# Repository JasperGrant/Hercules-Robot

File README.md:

# Hercules Robot

Seen here with sunglasses

Design project for ECED3901.

2nd place winner of the Gregson Robotic Design Competition.

Team consists of Andy Doucet, Spencer Dugas, and Jasper Grant.

# Problem

The goal of the project is to create a robot to autonomously capture and dispose of mines while navigating a maze and avoiding wildlife.

The robot will have to deal with randomly placed mines that must be defused before contact is made, and wildlife in the form of a carboard deer cutout which walks back and forth through the maze using a pulley system.

# High Level Robot Architecture

# Solution

Our robot's control code consisted of an esoteric programming language in which a 3x7x7 array of characters is interpreted as an executable. This array can be filled with cardinal directions or other symbols. Each array element points to the next element to be executed.

Once a mine is detected by the robot's limit switches, the robot will switch from following the forwards array, to the return array until the mine has been disposed of. Finally the robot will follow a third return array back to it's next position in the mine hunt.

The final program used for competition:
char map[NUMBEROFMAPS][MAPSIZE][MAPSIZE][MAXSTRINGLEN] = {
	"N", "E", "E", "S", "S", "N", "E",
  "", "E", "N", "M", "W", "W", "SEE",
  "", "N", "N", "N", "W", "W", "S",
  "", "", "", "", "", "M", "W",
  "", "", "", "N", "N", "E", "W",
  "", "", "", "M", "S", "N", "W",
  "", "", "N", "N", "W", "", "",
  
  "", "E", "N", "N", "E", "E", "S",
  "", "E", "W", "N", "E", "E", "S",
  "", "N", "e", "S", "S", "N", "E",
  "", "", "", "", "", "E", "E",
  "", "", "E", "S", "S", "S", "S",
  "", "", "R", "S", "E", "S", "S",
  "", "", "W", "S", "S", "", "",
  
  "", "WwNF", "WwNNWWSSEF", "WwNNWWSSF", "WwNNWWSF", "NNNWWH", "NNNWWH",
  "", "WwNF", "WwNNWSF", "EF", "WwNNWWF", "NNNWWH", "NNNWWH",
  "", "WwNF", "WwNF", "WwNNF", "WwNNWF", "NNNNWWWSWF", "NNNNWWWSF",
  "", "", "", "", "", "ENNF", "NNNNWWWF",
 	"", "", "", "WNNF", "WNNNF", "NNNF", "NNNNWWF",
  "", "", "", "WNF", "NF", "NNNNF", "NNNNWF",
  "", "", "ENF", "ENNF", "ENNWF", "NNNWWWWF", "NNNWWWWF"};
 
 # Optimization
 
 Path planning was done using Adaptive Monte Carlo Localization on a constantly kept up to date LIDAR map.
 Included in the repo also the most up to date and successful pathfinding parameters.

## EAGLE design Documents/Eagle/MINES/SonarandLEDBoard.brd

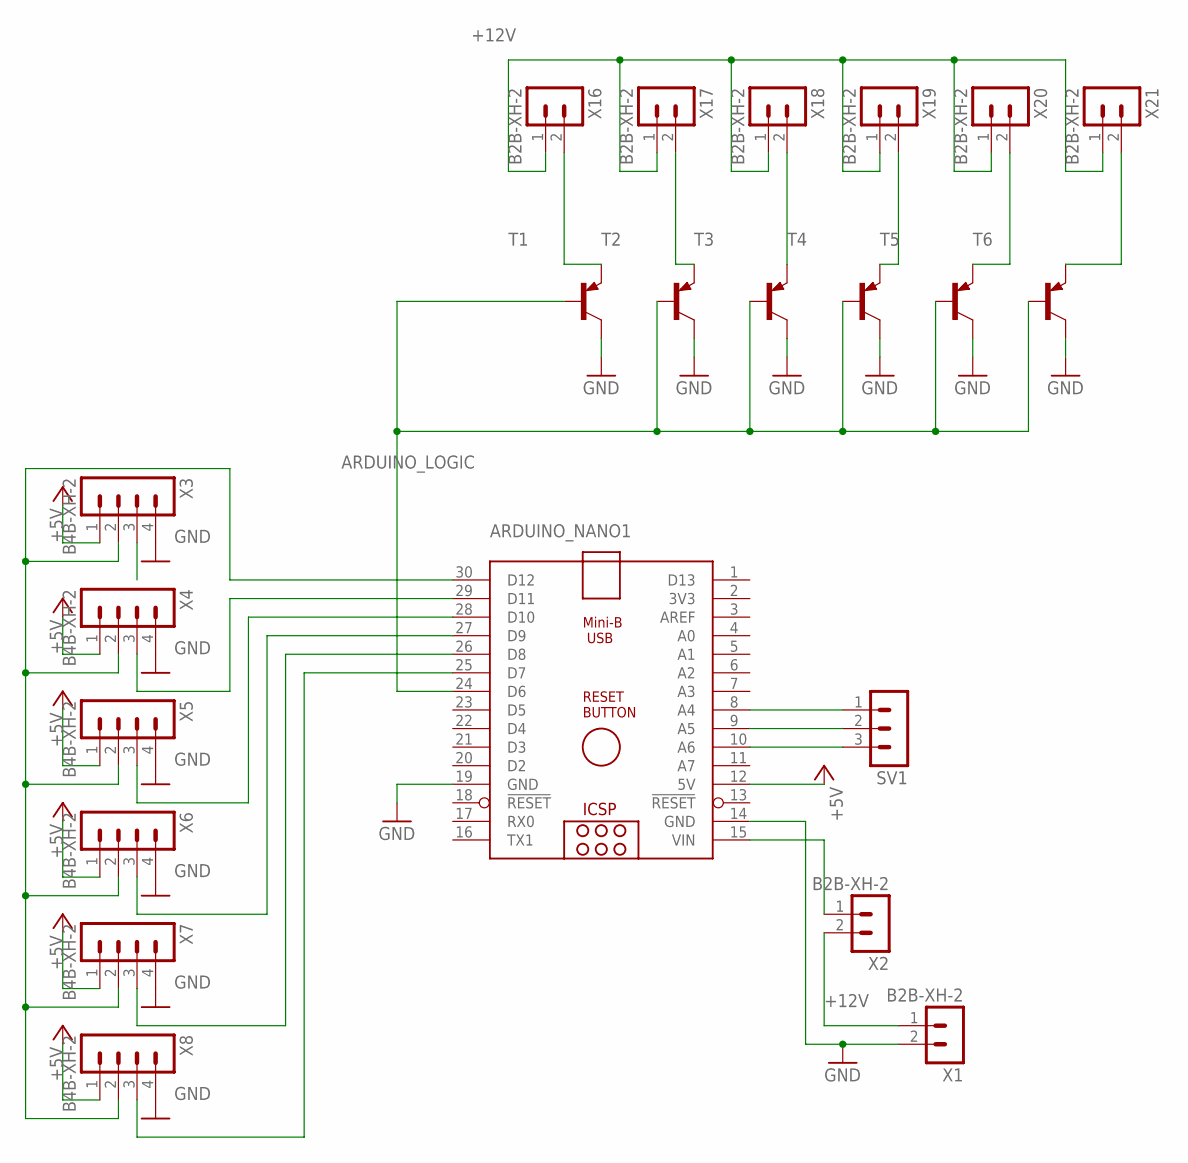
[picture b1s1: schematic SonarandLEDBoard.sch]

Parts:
ARDUINO_NANO1: ARDUINO_NANO
SV1: MA03-1
T1, T2, T3, T4, T5, T6: -PNP-TOP3V; TOP3V
X1, X2, X16, X17, X18, X19, X20, X21: B2B-XH-2; B2B-XH-A
X3, X4, X5, X6, X7, X8: B4B-XH-2; B4B-XH-A

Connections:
+5V: ARDUINO_NANO1.12 (5V), X3.1, X4.1, X5.1, X6.1, X7.1, X8.1
+12V: X1.1, X2.2, X16.1, X17.1, X18.1, X19.1, X20.1, X21.1
ARDUINO_LOGIC: ARDUINO_NANO1.24 (D6), T1.B, T2.B, T3.B, T4.B, T5.B, T6.B
GND: ARDUINO_NANO1.14 (GND), ARDUINO_NANO1.19 (GND), T1.C, T2.C, T3.C, T4.C, T5.C, T6.C, X1.2, X3.4, X4.4, X5.4, X6.4, X7.4, X8.4
unnamed: ARDUINO_NANO1.8 (A4), SV1.1
unnamed: ARDUINO_NANO1.15 (VIN), X2.1
unnamed: ARDUINO_NANO1.9 (A5), SV1.2
unnamed: ARDUINO_NANO1.10 (A6), SV1.3
unnamed: T1.E, X16.2
unnamed: ARDUINO_NANO1.26 (D8), X7.3
unnamed: ARDUINO_NANO1.29 (D11), X4.3
unnamed: ARDUINO_NANO1.28 (D10), X5.3
unnamed: T2.E, X17.2
unnamed: ARDUINO_NANO1.27 (D9), X6.3
unnamed: T3.E, X18.2
unnamed: T4.E, X19.2
unnamed: ARDUINO_NANO1.30 (D12), X3.2, X4.2, X5.2, X6.2, X7.2, X8.2
unnamed: ARDUINO_NANO1.25 (D7), X8.3
unnamed: T5.E, X20.2
unnamed: T6.E, X21.2

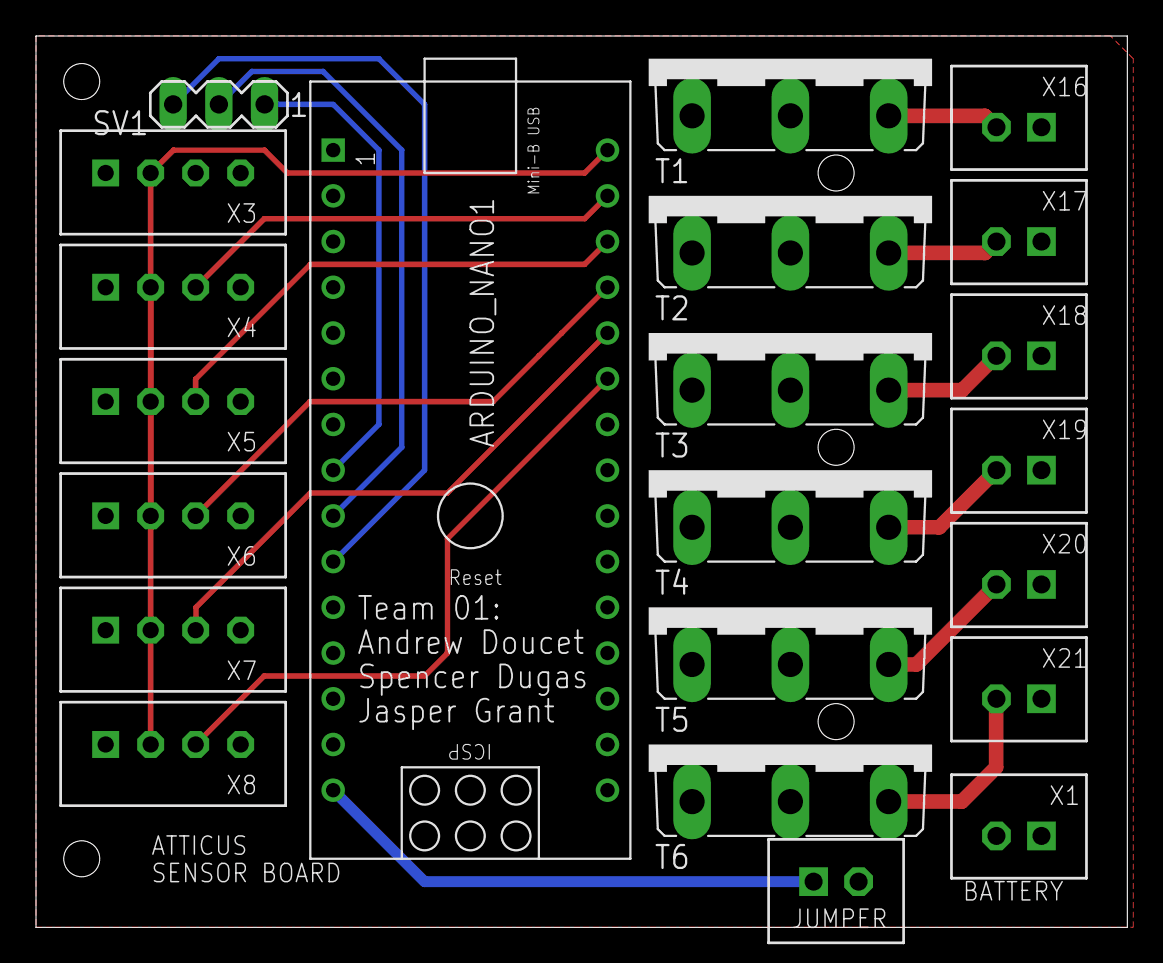
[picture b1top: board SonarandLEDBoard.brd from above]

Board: 2 copper layers, 60.6 x 49.5 mm, 22 parts (0 on the bottom side), 20 nets.

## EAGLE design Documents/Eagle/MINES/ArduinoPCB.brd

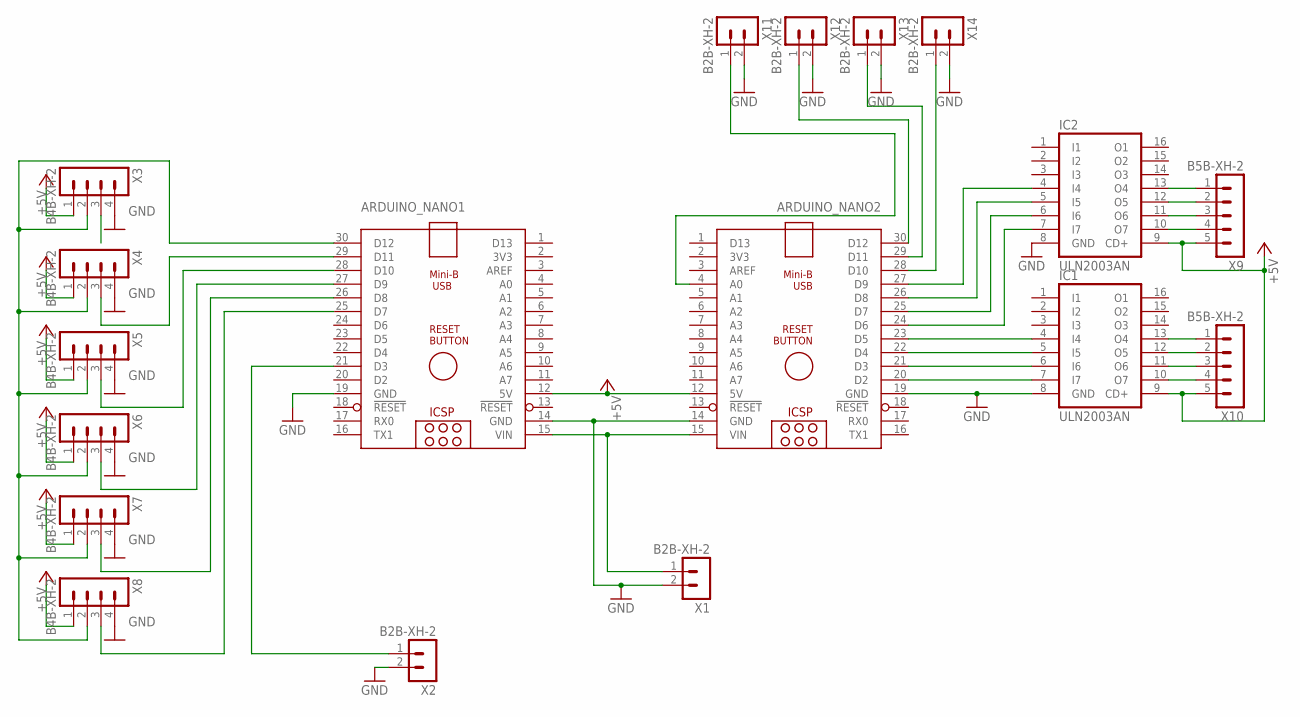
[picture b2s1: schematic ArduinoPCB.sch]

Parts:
ARDUINO_NANO1, ARDUINO_NANO2: ARDUINO_NANO
IC1, IC2: ULN2003AN; DIL16
X1, X2, X11, X12, X13, X14: B2B-XH-2; B2B-XH-A
X3, X4, X5, X6, X7, X8: B4B-XH-2; B4B-XH-A
X9, X10: B5B-XH-2; B5B-XH-A

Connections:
+5V: ARDUINO_NANO1.12 (5V), ARDUINO_NANO2.12 (5V), IC1.9 (CD+), IC2.9 (CD+), X3.1, X4.1, X5.1, X6.1, X7.1, X8.1, X9.5, X10.5
GND: ARDUINO_NANO1.14 (GND), ARDUINO_NANO1.19 (GND), ARDUINO_NANO2.14 (GND), ARDUINO_NANO2.19 (GND), IC1.8 (GND), IC2.8 (GND), X1.2, X2.2, X3.4, X4.4, X5.4, X6.4, X7.4, X8.4, X11.2, X12.2, X13.2, X14.2
unnamed: ARDUINO_NANO2.29 (D11), X13.1
unnamed: IC1.10 (O7), X10.4
unnamed: IC1.11 (O6), X10.3
unnamed: IC1.12 (O5), X10.2
unnamed: IC1.13 (O4), X10.1
unnamed: IC2.10 (O7), X9.4
unnamed: IC2.11 (O6), X9.3
unnamed: IC2.12 (O5), X9.2
unnamed: IC2.13 (O4), X9.1
unnamed: ARDUINO_NANO2.20 (D2), IC1.7 (I7)
unnamed: ARDUINO_NANO2.21 (D3), IC1.6 (I6)
unnamed: ARDUINO_NANO2.22 (D4), IC1.5 (I5)
unnamed: ARDUINO_NANO2.23 (D5), IC1.4 (I4)
unnamed: ARDUINO_NANO2.27 (D9), IC2.4 (I4)
unnamed: ARDUINO_NANO2.26 (D8), IC2.5 (I5)
unnamed: ARDUINO_NANO2.25 (D7), IC2.6 (I6)
unnamed: ARDUINO_NANO2.24 (D6), IC2.7 (I7)
unnamed: ARDUINO_NANO2.30 (D12), X12.1
unnamed: ARDUINO_NANO2.4 (A0), X11.1
unnamed: ARDUINO_NANO1.15 (VIN), ARDUINO_NANO2.15 (VIN), X1.1
unnamed: ARDUINO_NANO1.21 (D3), X2.1
unnamed: ARDUINO_NANO1.26 (D8), X7.3
unnamed: ARDUINO_NANO2.28 (D10), X14.1
unnamed: ARDUINO_NANO1.29 (D11), X4.3
unnamed: ARDUINO_NANO1.28 (D10), X5.3
unnamed: ARDUINO_NANO1.27 (D9), X6.3
unnamed: ARDUINO_NANO1.30 (D12), X3.2, X4.2, X5.2, X6.2, X7.2, X8.2
unnamed: ARDUINO_NANO1.25 (D7), X8.3

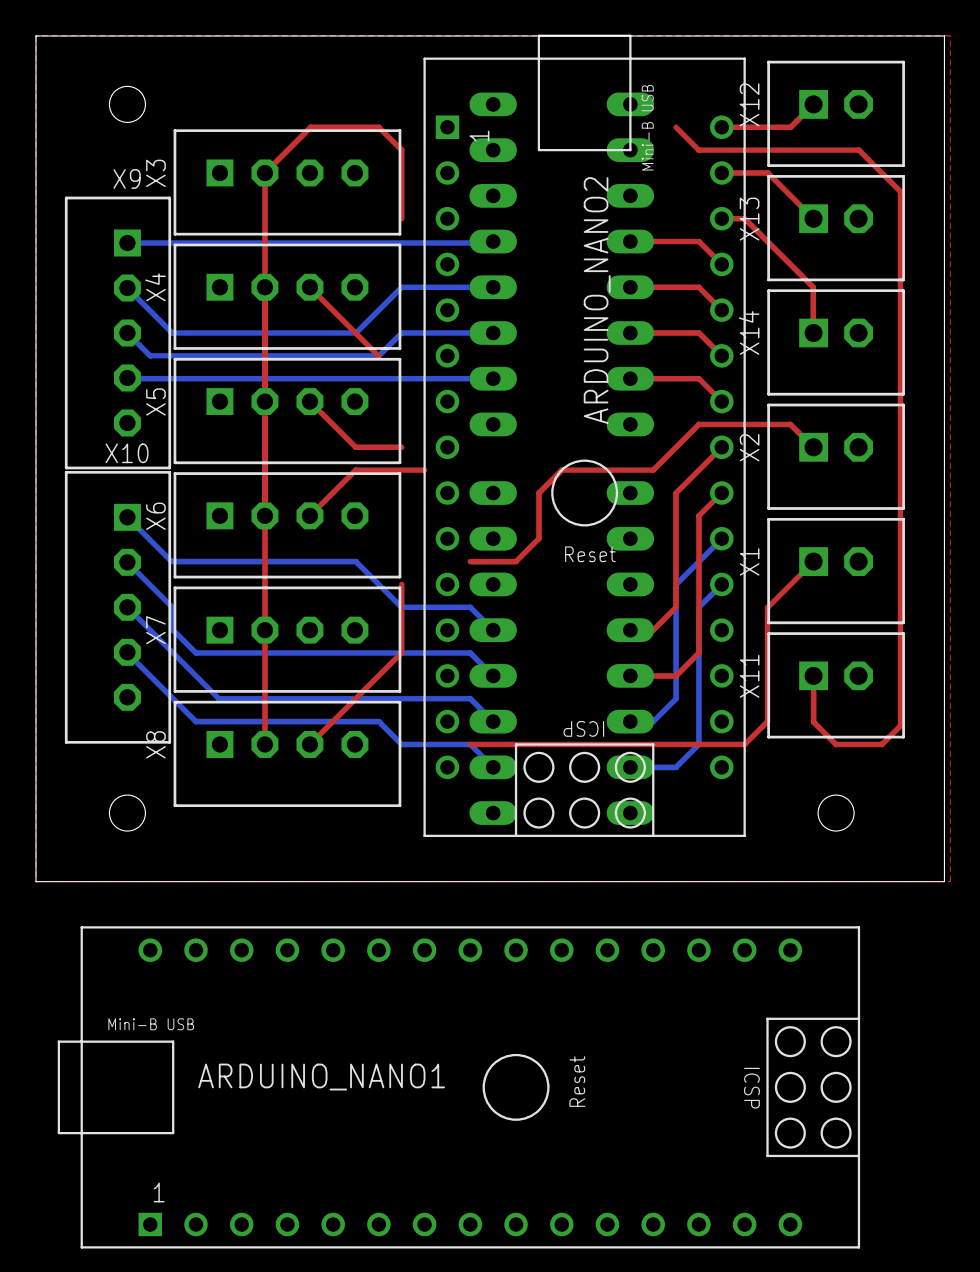
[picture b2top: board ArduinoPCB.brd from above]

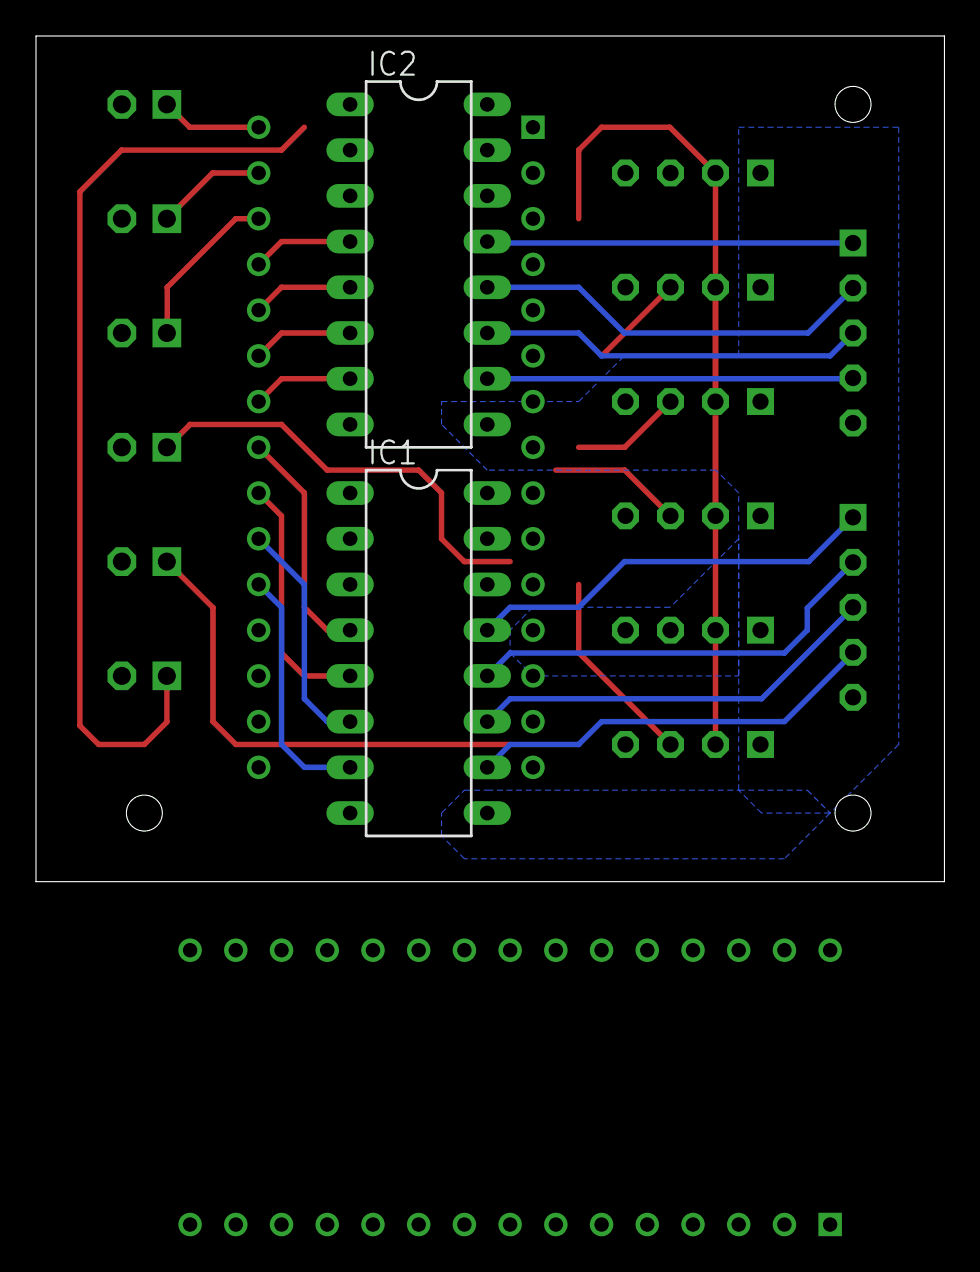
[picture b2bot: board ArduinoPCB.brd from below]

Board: 2 copper layers, 50.5 x 47.0 mm, 18 parts (2 on the bottom side), 30 nets.

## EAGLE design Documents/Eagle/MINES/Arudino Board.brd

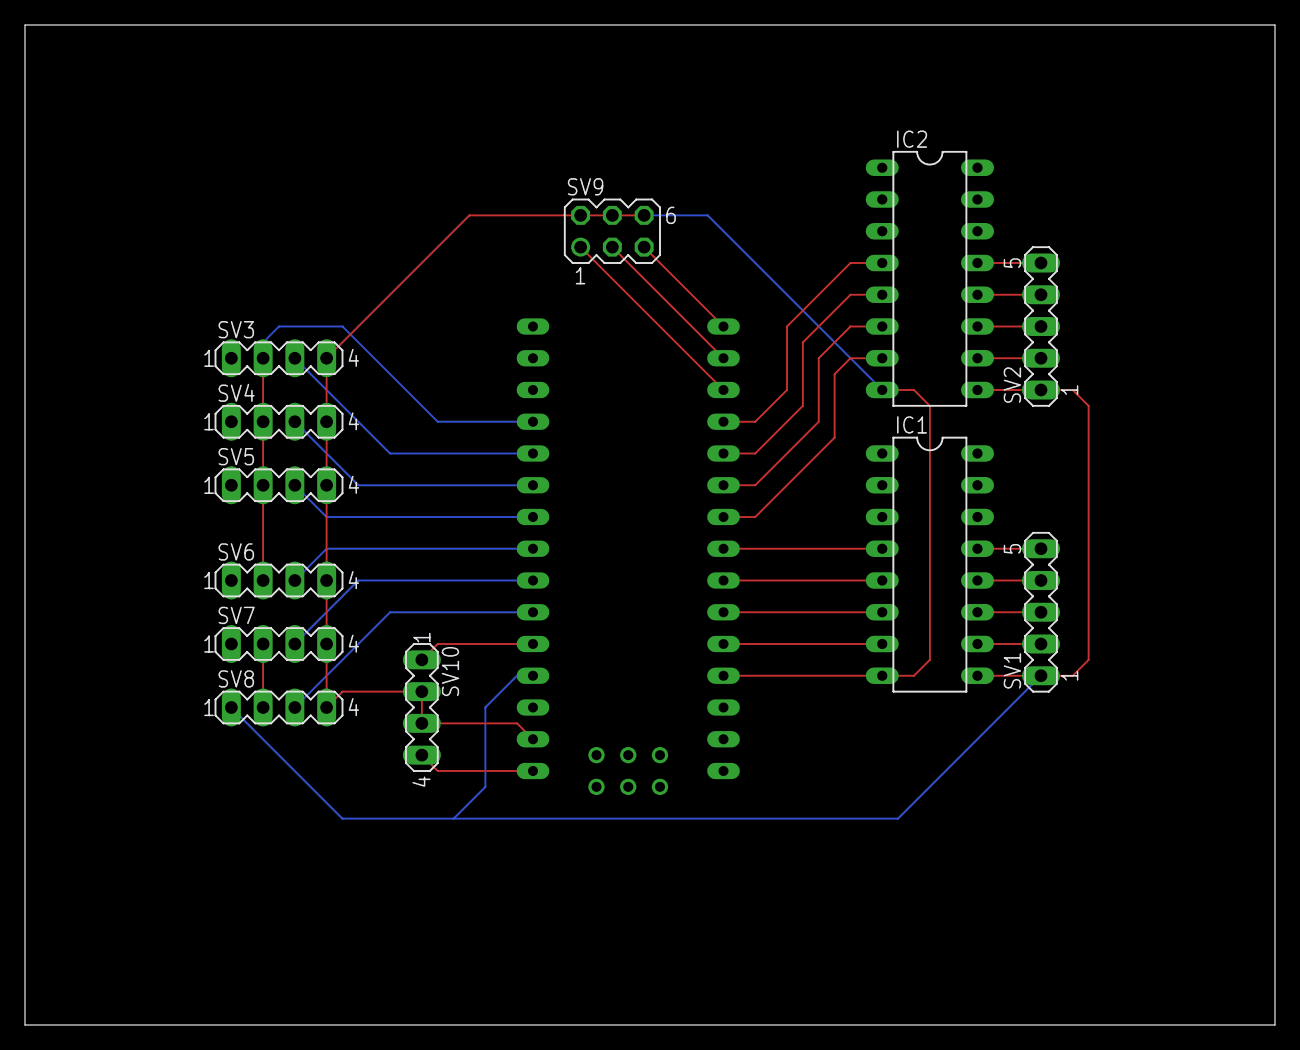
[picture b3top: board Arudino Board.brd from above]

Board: 2 copper layers, 100.0 x 80.0 mm, 13 parts (0 on the bottom side), 30 nets.

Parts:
IC1, IC2: ULN2003AN; DIL16
SV1, SV2: MA05-1
SV3, SV4, SV5, SV6, SV7, SV8, SV10: MA04-1
SV9: MA03-2
U$2: NANO

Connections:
+5V: IC1.9, IC2.9, SV1.1, SV2.1, SV3.1, SV4.1, SV5.1, SV6.1, SV7.1, SV8.1, U$2.5V
GND: IC1.8, IC2.8, SV3.4, SV4.4, SV5.4, SV6.4, SV7.4, SV8.4, SV9.2, SV9.4, SV9.6, SV10.2, SV10.3, U$2.GND, U$2.GND1
unnamed: SV9.3, U$2.D11
unnamed: IC1.10, SV1.2
unnamed: IC1.11, SV1.3
unnamed: IC1.12, SV1.4
unnamed: IC1.13, SV1.5
unnamed: IC2.10, SV2.2
unnamed: IC2.11, SV2.3
unnamed: IC2.12, SV2.4
unnamed: IC2.13, SV2.5
unnamed: IC1.7, U$2.D2
unnamed: IC1.6, U$2.D3
unnamed: IC1.5, U$2.D4
unnamed: IC1.4, U$2.D5
unnamed: IC2.4, U$2.D9
unnamed: IC2.5, U$2.D8
unnamed: IC2.6, U$2.D7
unnamed: IC2.7, U$2.D6
unnamed: SV9.5, U$2.D12
unnamed: SV10.4, U$2.RAW
unnamed: SV5.3, U$2.A3
unnamed: SV10.1, U$2.A7
unnamed: SV7.3, U$2.A5
unnamed: SV3.3, U$2.A1
unnamed: SV9.1, U$2.D10
unnamed: SV4.3, U$2.A2
unnamed: SV6.3, U$2.A4
unnamed: SV3.2, SV4.2, SV5.2, SV6.2, SV7.2, SV8.2, U$2.A0
unnamed: SV8.3, U$2.A6

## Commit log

2022-05-06 Initial commit after package creation
2022-05-06 Copied the publishing node from tutorial
2022-05-06 Made talker.py executable
2022-05-06 Slowed down display rate
2022-05-06 commit
    Wonderful message
2022-05-06 Amazing message
2022-05-20 Added a README.md to keep track of programs.
2022-05-20 Copied faulty code provided by instructor.
2022-05-23 Changed pi/4 to pi/2 in the rotation function
2022-05-24 Rotating problem fixed ONLY CLOCKWISE ROTATION
2022-05-26 Old code from lab 3
2022-05-26 Wrote Counter-Clockwise path
2022-05-26 Extended Andy's code to go both directions
2022-05-26 Added sleep function and fixed pi
2022-05-26 Added constants, updated code to actually work
2022-05-26 Maybe fixed problem with odom?
2022-05-26 Added and updated fintunning coeficcients
2022-05-26 Reversed CW and CCW directions
2022-05-27 Changed finetunninage for lab rectangle and added last spin
2022-05-27 Added launch file for lab 4
2022-05-27 Added formatted LIDAR readings and python script that made them
2022-05-27 Took out dashes
2022-05-27 Added world and model for lab 4
2022-05-27 Added proper model from lab
2022-05-27 Changed model
2022-05-27 Fixed merge issues
2022-05-27 Added first map
2022-05-27 Added Second Map
2022-05-31 Added a launch file
2022-05-31 Changed movement path for dt2
2022-05-31 Changed launch file
2022-06-01 Dt2 launch file problem fixed
2022-06-03 A bunch of Jasper changes
2022-06-03 Made changes to mistakes I made
2022-06-03 Fixed Gazebo stuff
2022-06-03 Commented thing in launch file
2022-06-10 Updated parameters for Robot pathplanner
2022-06-15 Got dt3 to work in gazebo
2022-06-16 Added coefs to the cpp code
2022-06-16 Wrote "odom"
2022-06-16 Added Eagle files
2022-06-16 made changes to code
2022-06-16 Got robot to use global mapping
2022-06-16 Made code better with functions
2022-06-17 Updated EAGLE PCB board
2022-06-17 Changed grid and updated code
2022-06-17 Fixed lab 3 launch file
2022-06-17 Put 2 arduinos in eagle
2022-06-20 Finished Arm and Sensor Boards
2022-06-20 Arduino Code shenanigans
2022-06-21 Added 3-head breakouts to both boards and team name
2022-06-21 Added gerbers
2022-06-28 Arduino Stuff
2022-07-04 Arduino Shenans
2022-07-05 More Arduino Stuff
2022-07-06 Updated robot movement algorithm
2022-07-07 Added proper pseudocode
2022-07-07 Added empty forward and reverse maps
2022-07-07 Added forward case
2022-07-08 Filled in Maps
2022-07-08 Added callbacks
2022-07-08 Fixed some bugs
2022-07-08 A bunch of stuff
2022-07-08 Mapped course
2022-07-08 Updated code to convert from metres to feet
2022-07-10 Solved a ton of code problems
2022-07-10 Final changes before reallife testing
2022-07-11 Added Sieben's params and changed some of ours
2022-07-12 Added dynamic footprint
2022-07-12 Jasper did stuff on my laptop
2022-07-12 Adjusted params and added offsets to code
2022-07-13 Jasper made the odometry work :)
2022-07-13 Jasper did stuff
2022-07-13 Made hopefully final map
2022-07-13 Reverted params
2022-07-13 Changed Launch & Cpp files
2022-07-13 Reverted launch files
2022-07-13 Used correct params
2022-07-13 dababy lets go
2022-07-13 Made new launch files
2022-07-13 Added hallway code
2022-07-13 Added H and h
2022-07-13 Finalized multiple changes to simple navigation goals
2022-07-13 Backup working params
2022-07-14 New map again
2022-07-14 Added tolerance parameters
2022-07-14 Added post-team meeting offsets
2022-07-14 Added post-team meeting offsets and dual mine dropoff waypoints
2022-07-14 Fixed hall
2022-07-14 Happy happy run
2022-07-14 Course completed in 12.44!!
2022-07-14 Added two new instructions
2022-07-14 Updated maps to use R and G
2022-07-14 Fizxed G and O
2022-07-14 Made modifcations to code after g test
2022-07-14 Made new offsets again
2022-07-15 Modified ofsets
2022-07-15 Fixed locating log
2022-07-15 Fixed mistakes in previous commit
2022-07-15 Hopefully fixed corner problem
2022-07-15 Semi-final version
2022-07-15 Semi Final Code v2
2022-07-15 I want to die
2022-07-15 Wont hit wildlife lol
2022-07-15 FINAL COMMIT
2022-07-20 EAGLE
